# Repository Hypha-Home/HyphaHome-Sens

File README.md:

# Der Hypha Home - Sens
Dieses DIY Projekt ist ein Multisensor und wie der Name schon sagt, besitzt er mehrere Sensoren:
* LD2410 für die Bewegungs und Präsenzerkennung
* SHT41 für die Temperatur und Luftfeuchtemessung
* SCD41 für die CO2 Messung
* BHT1750 für eine Lichtmessung
* ENS160 für eine VOC messung (enthalten ist auch ein AHT21, der aber nur für den ENS160 zuständig ist.)

## Ziele
* Ein Sensor pro Raum der schnell und zuverlässig Daten sendet.
* Ersatz für Raumthermostate. 
* Feste Spannungsversorgung (nicht Batteriebetrieben)
* Kostengünstig und flexibel in der Ausstattung

Der Sensor kann entweder mit einem Steckernetzteil oder (wer sowieso saniert/renoviert) an einer Unterputzdose mit fester 5-30VDC Spannungsversorgung montiert werden.

Mit dem SHT41 Temperatursensor und eingerichtetem WLAN kann der Hypha Home - Sens direkt mit einem Shelly kommunizieren und diesen steuern. Damit fungiert er ebenfalls als Raumthermostat für eine Fußbodenheizung oder eines Heizkörpers wenn der zuständige Stellantrieb über den Shelly gesteuert wird.

Alle Sensoren werden via MQTT an einen eigenen Broker geschickt. Für Home Assistant ist sogar ein Discovery Protokoll vorhanden. Damit ist eine Aufnahme in das Home Assistant Smart-Home kinderleicht. 

Im Home-Assistant kann man sich dann vieles ausdenken: 
* Das Licht bei bewegung einschalten, aber nur wenn hell genug ist. 
* Einen Alarm auslösen wenn die Luftqualität schlecht ist und es mal wieder zeit wäre zu lüften.
* ...

## Anleitungen
Wie ihr den Sensor baut, was ihr benötigt und wie ihr die Firmware auf den ESP flashen könnt, findet [hier](docs/onboarding/README.md)

## Aktuell umgesetzt
Aktuell befindet sich das Projekt im Prototypstadium. Die Software funktioniert schon sehr zuverlässig. Die Platine hat aber noch viele Mängel. Hier wird es eine neue Revision geben. Auch das Gehäuse ist noch sehr rudimentär. 
> Vor allem beim Platinen- und Gehäusedesign würde ich mich über unterstützung freuen! 

Aktuell befinden sich 2 Prototypen bei mir im Haus im einsatz (seit knapp 20 Tagen) und verrichten dort einen schon sehr zuverlässigen Dienst. Das Licht schaltet schnell ein und auch nur dann wenn es gebraucht wird (zu dunkel). Die Heizungssteuerung funktioniert auch, wenn auch noch sehr rudimentär! Und damit kommen wir zu dem was noch fehlt:

## Was noch fehlt
Die Heizungssteuerung wird noch neue Modi, basierend auf einer 2-Punkt steuerung und einer PWM Steuerung, erhalten. 
Ebenfalls soll der Sens direkt die Lichtsteuerung über einen Shelly übernehmen können. (Diese Funktionen sind nur verbaut, wenn z.B. das Home Assistant ausfällt, sollen Kernfunktionen weiterhin bereitstehen)

## Besondere funktionen (ungetestet)
### Brandfrüherkennung
Der sensor kann anhand der Temperatur, des CO2 Werts und den VOC Wertes erkennen ob es im Raum ggf. brennt. Dies ist keine sher genaue Meldung und vor allem ersetzt es keineswegs einen zertifizierten Rauchmelder. Aber es kann dennoch helfen. Bei mir gab es bisher keinen Fehlalarm. Aber auch keinen wirklichen Alarm (zum Glück)

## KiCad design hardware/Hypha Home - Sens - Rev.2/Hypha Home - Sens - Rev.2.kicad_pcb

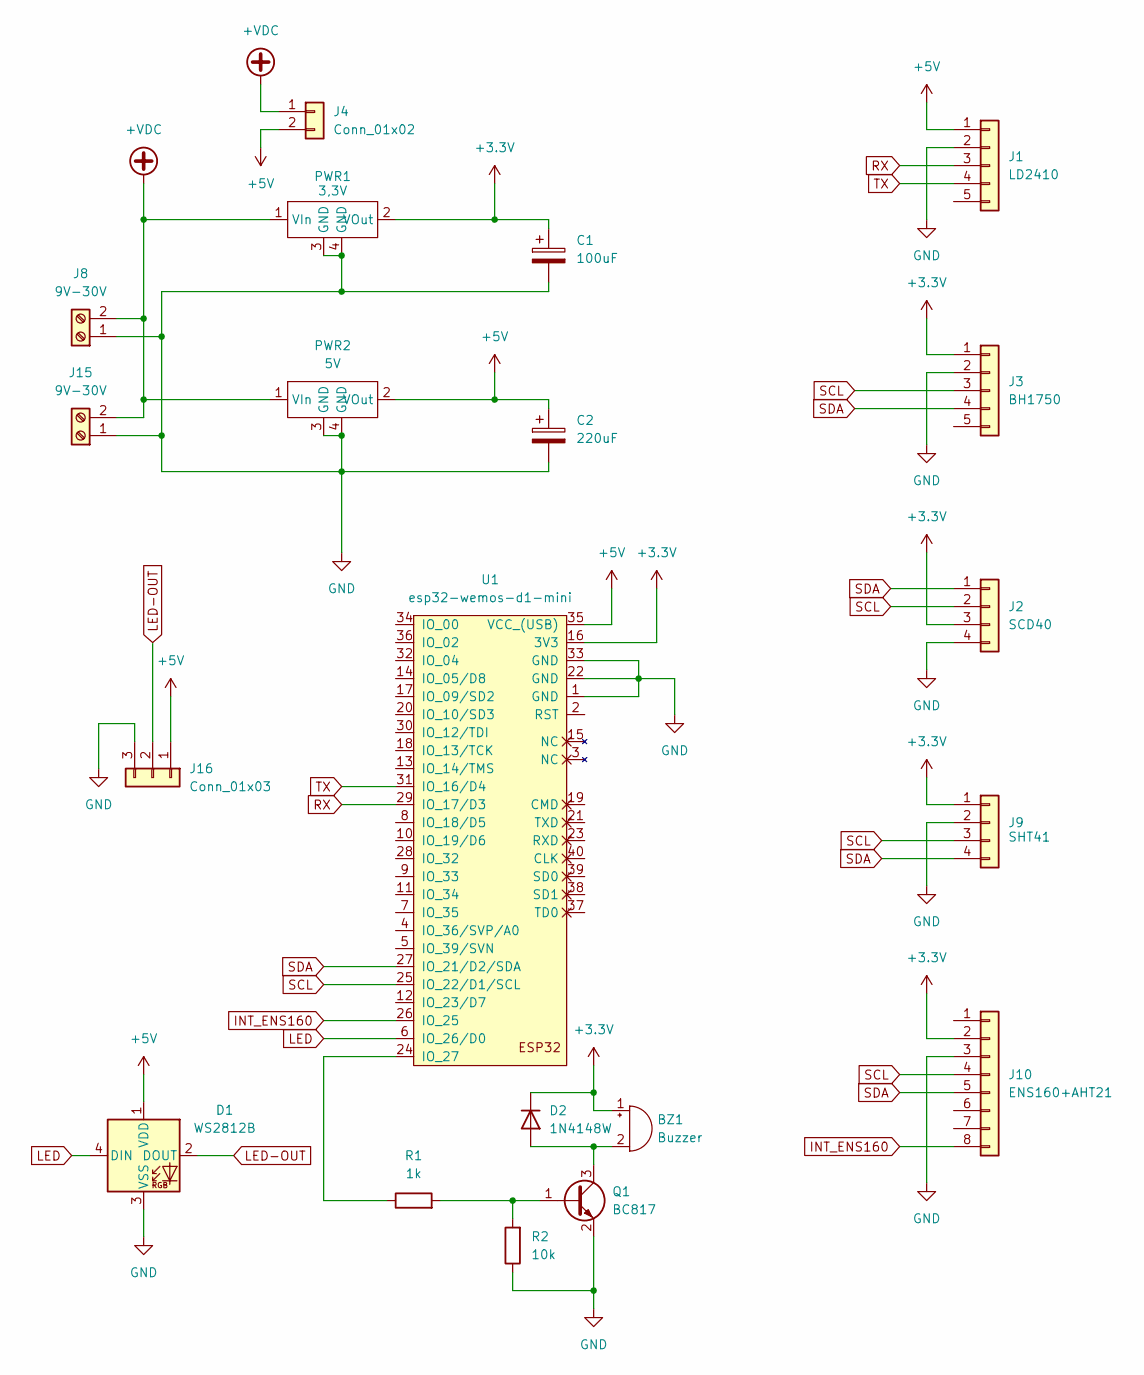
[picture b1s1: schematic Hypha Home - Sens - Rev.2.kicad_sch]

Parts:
BZ1: Buzzer; Buzzer_D9_RM5
C1: 100uF; CP_Radial_D5.0mm_P2.00mm
C2: 220uF; CP_Radial_D6.3mm_P2.50mm
D1: WS2812B; LED_WS2812B_PLCC4_5.0x5.0mm_P3.2mm
D2: 1N4148W; D_SOD-323_HandSoldering
J1: LD2410; PinHeader_1x05_P1.27mm_Vertical
J2: SCD40; PinHeader_1x04_P2.54mm_Vertical
J3: BH1750; PinHeader_1x05_P2.54mm_Vertical
J4: Conn_01x02; PinHeader_1x02_P2.54mm_Vertical
J8, J15: 9V-30V; TerminalBlock_MaiXu_MX126-5.0-02P_1x02_P5.00mm
J9: SHT41; PinHeader_1x04_P2.54mm_Vertical
J10: ENS160+AHT21; PinHeader_1x08_P2.54mm_Vertical
J16: Conn_01x03; PinHeader_1x03_P2.54mm_Vertical
PWR1: 3,3V; Spannungswandler
PWR2: 5V; Spannungswandler
Q1: BC817; SOT-23
R1: 1k; R_0805_2012Metric
R2: 10k; R_0805_2012Metric
U1: esp32-wemos-d1-mini

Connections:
+3.3V: BZ1.1 (+), C1.1, D2.1 (K), J2.3, J3.1, J9.1, J10.2, PWR1.2 (VOut), U1.16 (3V3)
+5V: C2.1, D1.1 (VDD), J1.1, J4.2, J16.1, PWR2.2 (VOut), U1.35 (VCC_(USB))
+VDC: J4.1, J8.2, J15.2, PWR1.1 (VIn), PWR2.1 (VIn)
GND: C1.2, C2.2, D1.3 (VSS), J1.2, J2.4, J3.2, J8.1, J9.2, J10.3, J15.1, J16.3, PWR1.3 (GND), PWR1.4 (GND), PWR2.3 (GND), PWR2.4 (GND), Q1.2 (E), R2.1, U1.1 (GND), U1.22 (GND), U1.33 (GND)
INT_ENS160: J10.8, U1.26 (IO_25)
LED: D1.4 (DIN), U1.6 (IO_26/D0)
LED-OUT: D1.2 (DOUT), J16.2
unnamed: BZ1.2 (-), D2.2 (A), Q1.3 (C)
unnamed: Q1.1 (B), R1.2, R2.2
unnamed: R1.1, U1.24 (IO_27)
RX: J1.3, U1.29 (IO_17/D3)
SCL: J2.2, J3.3, J9.3, J10.4, U1.25 (IO_22/D1/SCL)
SDA: J2.1, J3.4, J9.4, J10.5, U1.27 (IO_21/D2/SDA)
TX: J1.4, U1.31 (IO_16/D4)

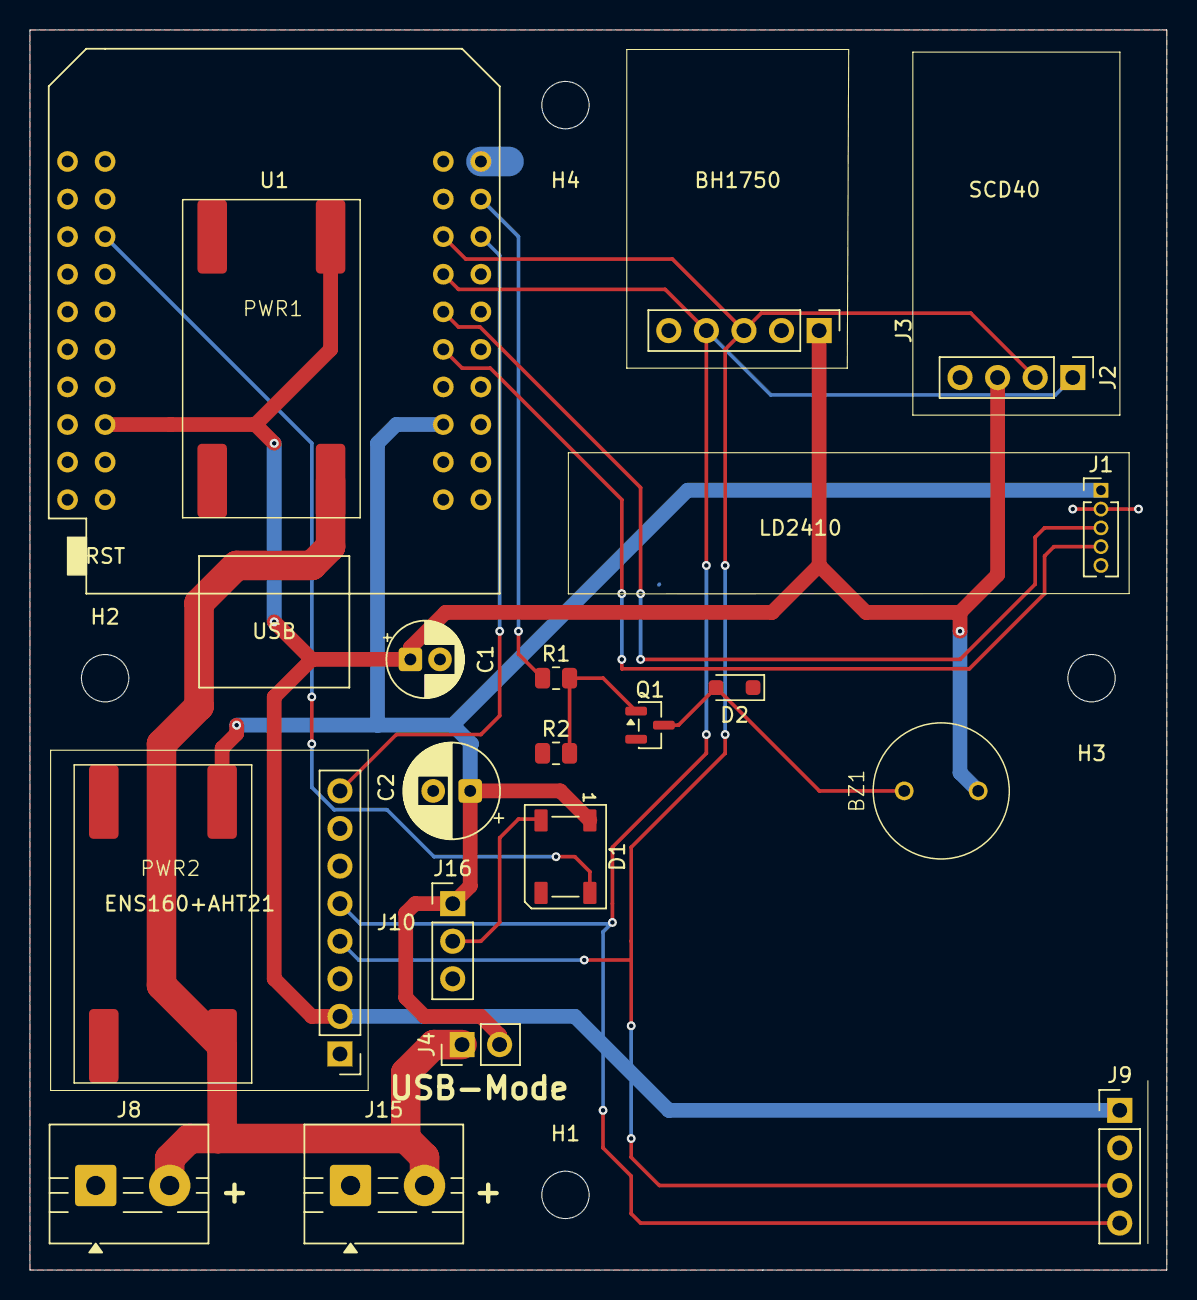
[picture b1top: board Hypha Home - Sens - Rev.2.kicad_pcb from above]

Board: 2 copper layers, 76.8 x 83.8 mm, 24 parts (0 on the bottom side), 14 nets.

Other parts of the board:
H1, H2, H3, H4: MountingHole_3.2mm_M3

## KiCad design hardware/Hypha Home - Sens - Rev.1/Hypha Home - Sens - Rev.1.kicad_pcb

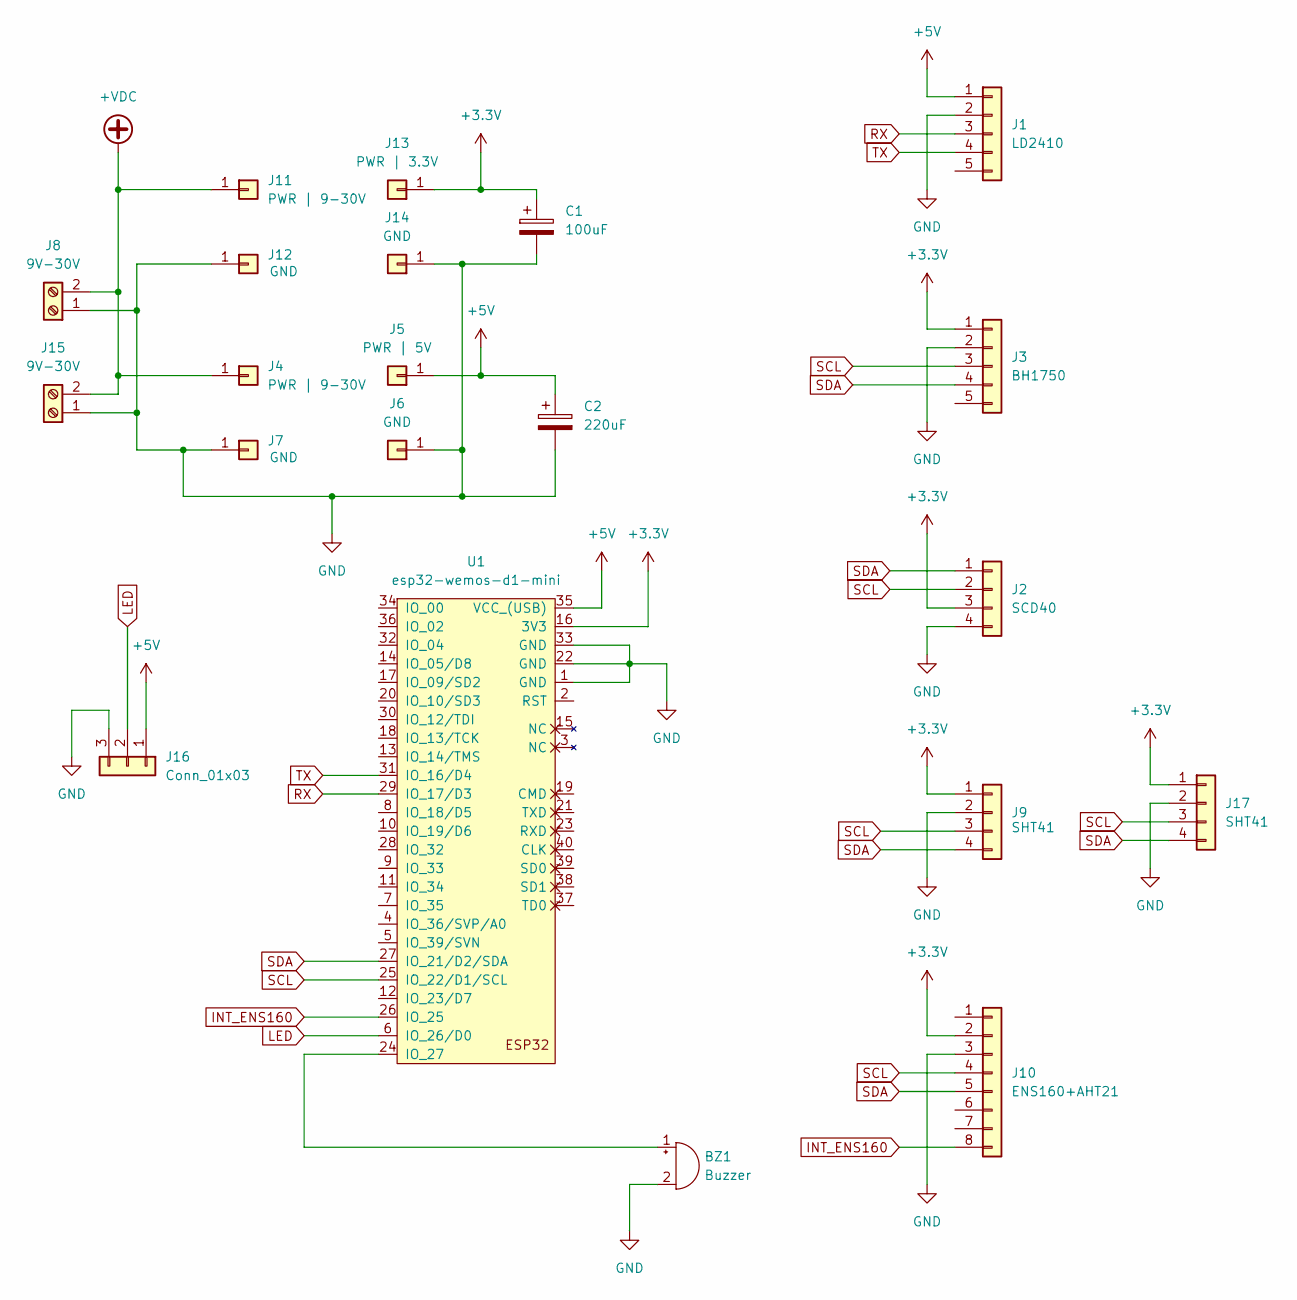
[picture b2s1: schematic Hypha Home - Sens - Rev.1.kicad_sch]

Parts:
BZ1: Buzzer; Buzzer_D9_RM5
C1: 100uF; CP_Radial_D5.0mm_P2.00mm
C2: 220uF; CP_Radial_D6.3mm_P2.50mm
J1: LD2410; PinHeader_1x05_P1.27mm_Vertical
J2: SCD40; PinHeader_1x04_P2.54mm_Vertical
J3: BH1750; PinHeader_1x05_P2.54mm_Vertical
J4, J11: PWR | 9-30V; PinHeader_1x01_P2.54mm_Vertical
J5: PWR | 5V; PinHeader_1x01_P2.54mm_Vertical
J6, J7, J12, J14: GND; PinHeader_1x01_P2.54mm_Vertical
J8, J15: 9V-30V; TerminalBlock_MaiXu_MX126-5.0-02P_1x02_P5.00mm
J9, J17: SHT41; PinHeader_1x04_P2.54mm_Vertical
J10: ENS160+AHT21; PinHeader_1x08_P2.54mm_Vertical
J13: PWR | 3.3V; PinHeader_1x01_P2.54mm_Vertical
J16: Conn_01x03; PinHeader_1x03_P2.54mm_Vertical
U1: esp32-wemos-d1-mini

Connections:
+3.3V: C1.1, J2.3, J3.1, J9.1, J10.2, J13.1 (Pin_1_1), J17.1, U1.16 (3V3)
+5V: C2.1, J1.1, J5.1 (Pin_1_1), J16.1, U1.35 (VCC_(USB))
+VDC: J4.1 (Pin_1_1), J8.2, J11.1 (Pin_1_1), J15.2
GND: BZ1.2 (-), C1.2, C2.2, J1.2, J2.4, J3.2, J6.1 (Pin_1_1), J7.1 (Pin_1_1), J8.1, J9.2, J10.3, J12.1 (Pin_1_1), J14.1 (Pin_1_1), J15.1, J16.3, J17.2, U1.1 (GND), U1.22 (GND), U1.33 (GND)
INT_ENS160: J10.8, U1.26 (IO_25)
LED: J16.2, U1.6 (IO_26/D0)
unnamed: BZ1.1 (+), U1.24 (IO_27)
RX: J1.3, U1.29 (IO_17/D3)
SCL: J2.2, J3.3, J9.3, J10.4, J17.3, U1.25 (IO_22/D1/SCL)
SDA: J2.1, J3.4, J9.4, J10.5, J17.4, U1.27 (IO_21/D2/SDA)
TX: J1.4, U1.31 (IO_16/D4)

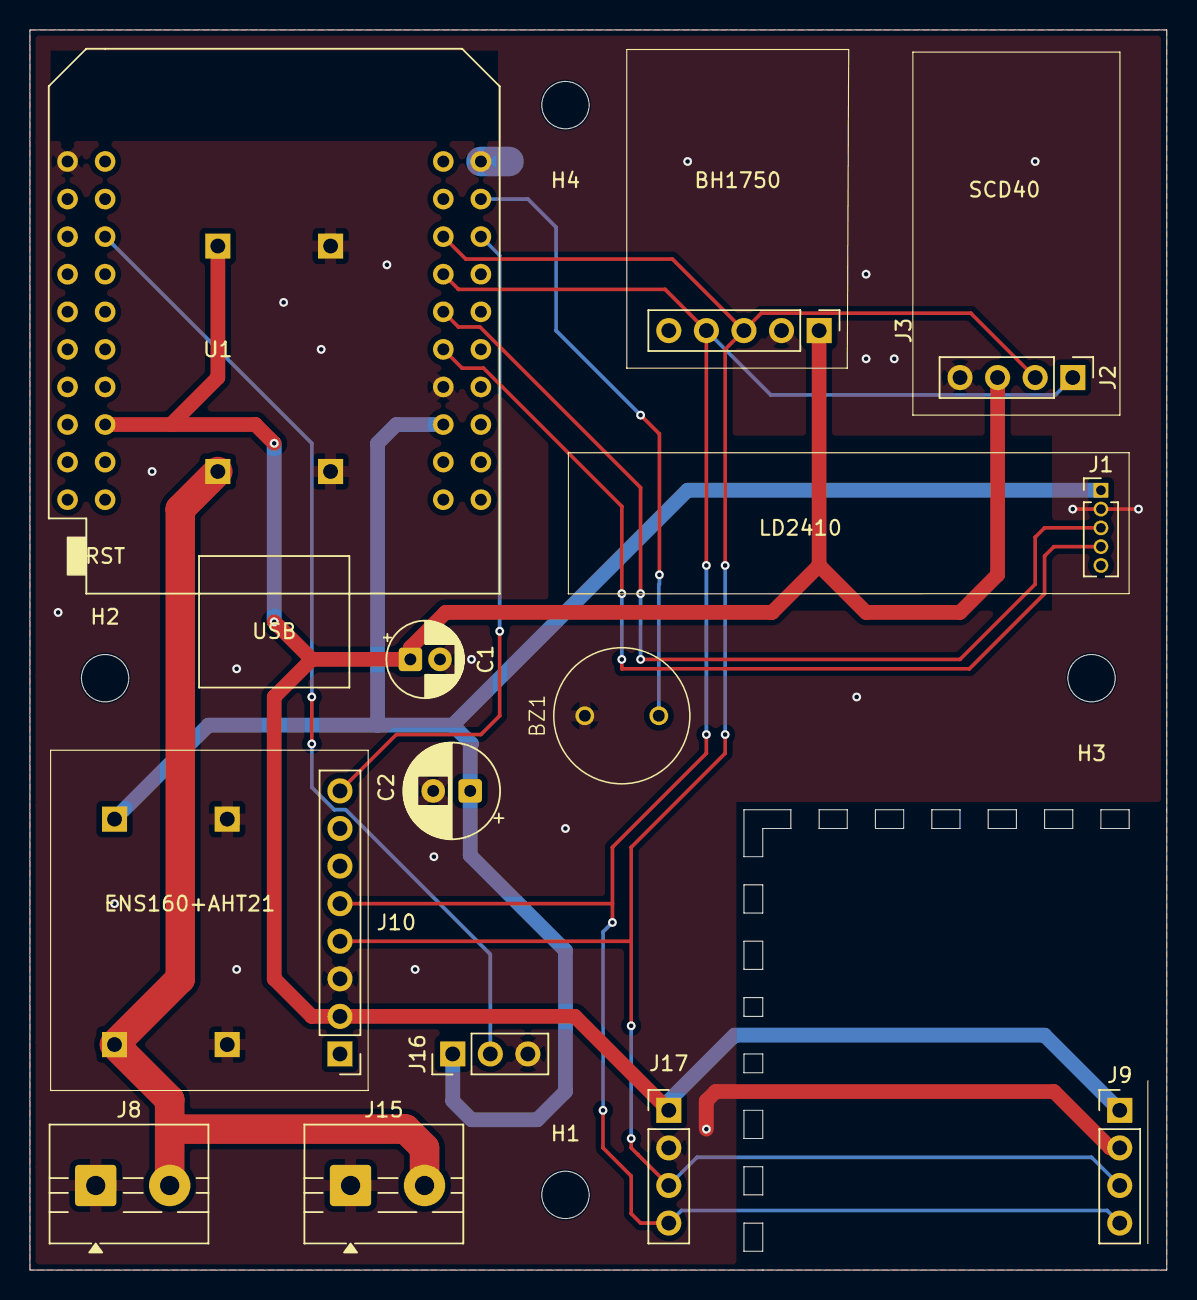
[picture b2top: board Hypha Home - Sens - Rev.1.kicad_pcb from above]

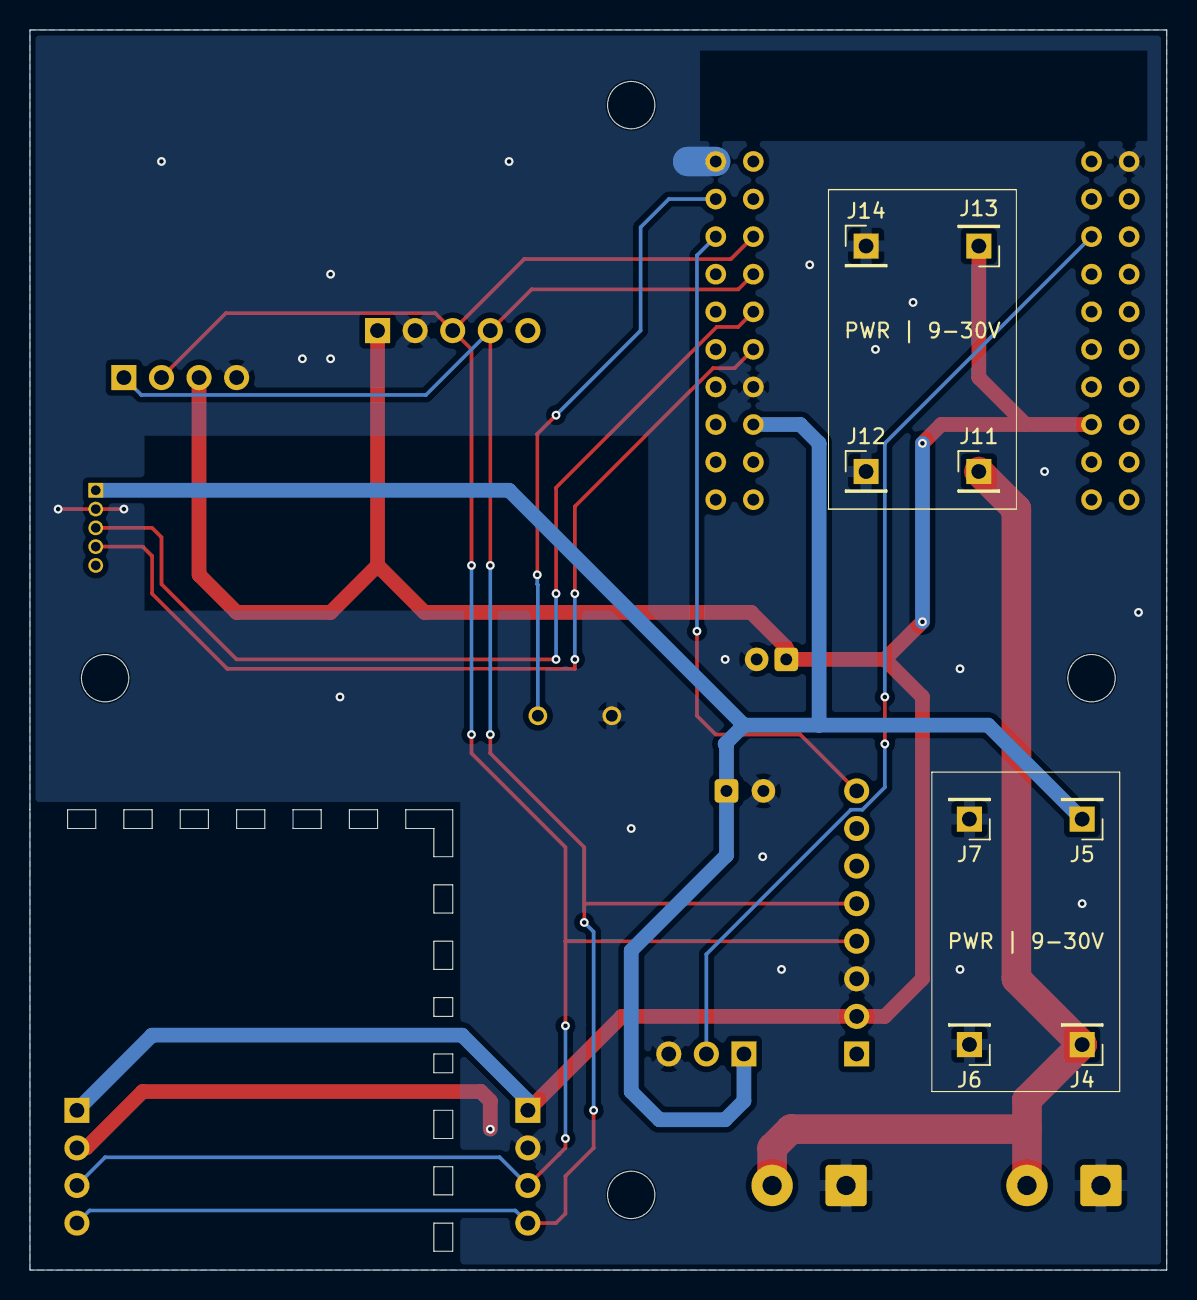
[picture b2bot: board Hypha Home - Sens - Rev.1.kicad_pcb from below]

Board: 2 copper layers, 76.8 x 83.8 mm, 25 parts (8 on the bottom side), 11 nets.

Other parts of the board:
H1, H2, H3, H4: MountingHole_3.2mm_M3
